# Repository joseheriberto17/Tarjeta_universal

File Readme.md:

# SSD1306 – UML del flujo actual (Mermaid)
**Autor:** jose heriberto  
**Fecha:** 2025-09-14  
**Propósito:** Documentar el flujo real del proyecto (init, armado de buffers, envío I²C, texto/figuras y scroll).  
**Ámbito:** App (main.c), Driver SSD1306 (cmd/ensamble), HAL/ASF (TWI0, PIO, PMC, SysTick).  
**Refs:** `SSD1306_cmd.c`, `SSD1306.h`, `main.c`

---

## 1) Vista de componentes (capas y dependencias)
```mermaid
flowchart TB
  subgraph App["App (main.c)"]
    Minit["sysclk_init/board_init\nconfigure_systick()\nconfigure_pins()"]
    Mdraw["Secuencia de dibujo:\nInicialize_SSD1306_default()\nNew_page()/frase_*/form_hearts()/vaciados()\nscroll() -> ssd1306_write()"]
    UART["UART_Handler (ISR)\n- lee RHR, limpia errores\n- eco debug"]
  end

  subgraph Driver["Driver SSD1306 (lógica de comandos)"]
    CMD["SSD1306_cmd.c\n(Set_*, Activate/Deactivate_Scroll,\nSet_Page_Start_..., etc.)"]
    BUF["Ensamble de buffer TWI\n(0x80 cmd-cont, 0x00 cmd-last,\n0xC0 data-cont, 0x40 data-last)"]
  end

  subgraph HAL["HAL / ASF (ATSAM3X8E)"]
    TWI["TWI0 (twi_master_init/twi_master_write)\nconfigure_pins_TWI_SSD1306()"]
    PIO["PIO (LEDs, mapeo pines)"]
    PMC["PMC clocks"]
    SysTick["SysTick (millis)"]
  end

  App --> Driver
  Driver --> HAL
  UART --> App
  Mdraw --> CMD
  CMD --> BUF
  Mdraw --> TWI
  BUF --> TWI
  Minit --> PMC
  Minit --> PIO
  Minit --> SysTick
```

---

## 2) Secuencia – Arranque e inicialización
```mermaid
sequenceDiagram
  autonumber
  participant Main as main.c
  participant HAL as HAL/ASF (PMC/PIO/SysTick)
  participant TWIc as configure_pins_TWI_SSD1306()
  participant CMD as Inicialize_SSD1306_default()
  participant BUF as Armado de buffer (0x80/0x00)
  participant I2C as ssd1306_write() / TWI0

  Main->>HAL: sysclk_init(), board_init()
  Main->>HAL: configure_systick()
  Main->>HAL: configure_pins() (LEDs)
  Main->>TWIc: configurar TWI0 (100 kHz) + pines PA17/PA18
  Main->>CMD: Inicialize_SSD1306_default(buffer_TWI, &len)
  activate CMD
  CMD->>BUF: Set_* cmds (AE, A8, D3, 40, A1, C8, DA, 81, A4/A5, A6/A7, D5, 8D, AF)
  BUF-->>CMD: buffer_TWI con parejas [0x80|0x00, cmd]
  deactivate CMD
  Main->>I2C: ssd1306_write(buffer_TWI, len*2)
  I2C-->>Main: status
```

---

## 3) Secuencia – Renderizado por páginas (texto/figuras/limpios y scroll)
```mermaid
sequenceDiagram
  autonumber
  participant Main as main.c
  participant CMD as New_page()/frase_A/B/C()/form_hearts()/vaciados()/scroll()
  participant BUF as Armado de buffer (0x80 cmd / 0xC0 data)
  participant I2C as ssd1306_write()/TWI0

  Main->>CMD: New_page(..., PAGE_0)
  CMD->>BUF: [0x80, B0|page] ... ultimo con 0x00
  BUF-->>Main: buffer_TWI, len
  Main->>I2C: ssd1306_write()
  end

  Main->>CMD: form_hearts()
  CMD->>BUF: datos con 0xC0 (cont.) y 0x40 (ultimo)
  BUF-->>Main: buffer_TWI (len=256)
  Main->>I2C: ssd1306_write(buffer_TWI, len)

  Note over Main: Vaciar paginas 1,2,6
  loop por cada pagina {1,2,6}
    Main->>CMD: New_page(PAGE_n)
    CMD->>BUF: comando B0|page (0x80...0x00)
    Main->>I2C: ssd1306_write(cmd)

    Main->>CMD: vaciados() (datos 0x00)
    CMD->>BUF: datos 0xC0...0x40
    Main->>I2C: ssd1306_write(data)
  end
  end

  Note over Main: Frases en paginas 3,4,5
  loop frase_A/B/C
    Main->>CMD: New_page(PAGE_k)
    CMD->>BUF: B0|page (0x80...0x00)
    Main->>I2C: ssd1306_write(cmd)

    Main->>CMD: frase_X() -> memcpy glyphs (128B)
    CMD->>BUF: datos 0xC0...0x40
    Main->>I2C: ssd1306_write(data)
  end
  end

  Note over Main: Scroll horizontal
  Main->>CMD
  CMD->>BUF: 0x26/0x27 + parametros; 0x2F (activate)
  end
  BUF-->>Main: buffer_TWI cmds (0x80...0x00)
  Main->>I2C: ssd1306_write(cmds scroll)
```

---

## 4) Máquina de estados – Driver/flujo SSD1306
```mermaid
stateDiagram-v2
  [*] --> Reset

  state Reset {
    note right: HW/SW reset
  }

  Reset --> InitSequence: Inicialize_SSD1306_default()
  InitSequence --> Ready: AF (Display ON) OK
  InitSequence --> Error: NAK / timeout

  Ready --> Updating: New_page()/frase_*/form_hearts()/vaciados()\n-> ssd1306_write(data)
  Updating --> Ready: última página/último byte (0x40) OK
  Updating --> Error: NAK / write fail

  Ready --> Scrolling: scroll() -> (0x26/0x27 ... 0x2F)
  Scrolling --> Ready: Deactivate_Scroll (0x2E) o redraw
  Scrolling --> Error: NAK

  Error --> Reset: política de reintento (max N)
```

---

## 5) Actividad – Ensamblado de buffer TWI (comandos y datos)
```mermaid
flowchart LR
  A[Iniciar buffer_TWI] --> B{¿Tipo?}
  B -- Comando --> C[Escribir 0x80 (continuación)\npara todos menos el último]
  C --> D[Escribir CMD]
  D --> E{¿Último comando del bloque?}
  E -- Sí --> F[Usar 0x00 en el último CMD]
  E -- No --> B

  B -- Datos --> G[Escribir 0xC0 (continuación)\npara todos menos el último]
  G --> H[Escribir DATA]
  H --> I{¿Último dato del bloque?}
  I -- Sí --> J[Usar 0x40 en el último DATA]
  I -- No --> B
```

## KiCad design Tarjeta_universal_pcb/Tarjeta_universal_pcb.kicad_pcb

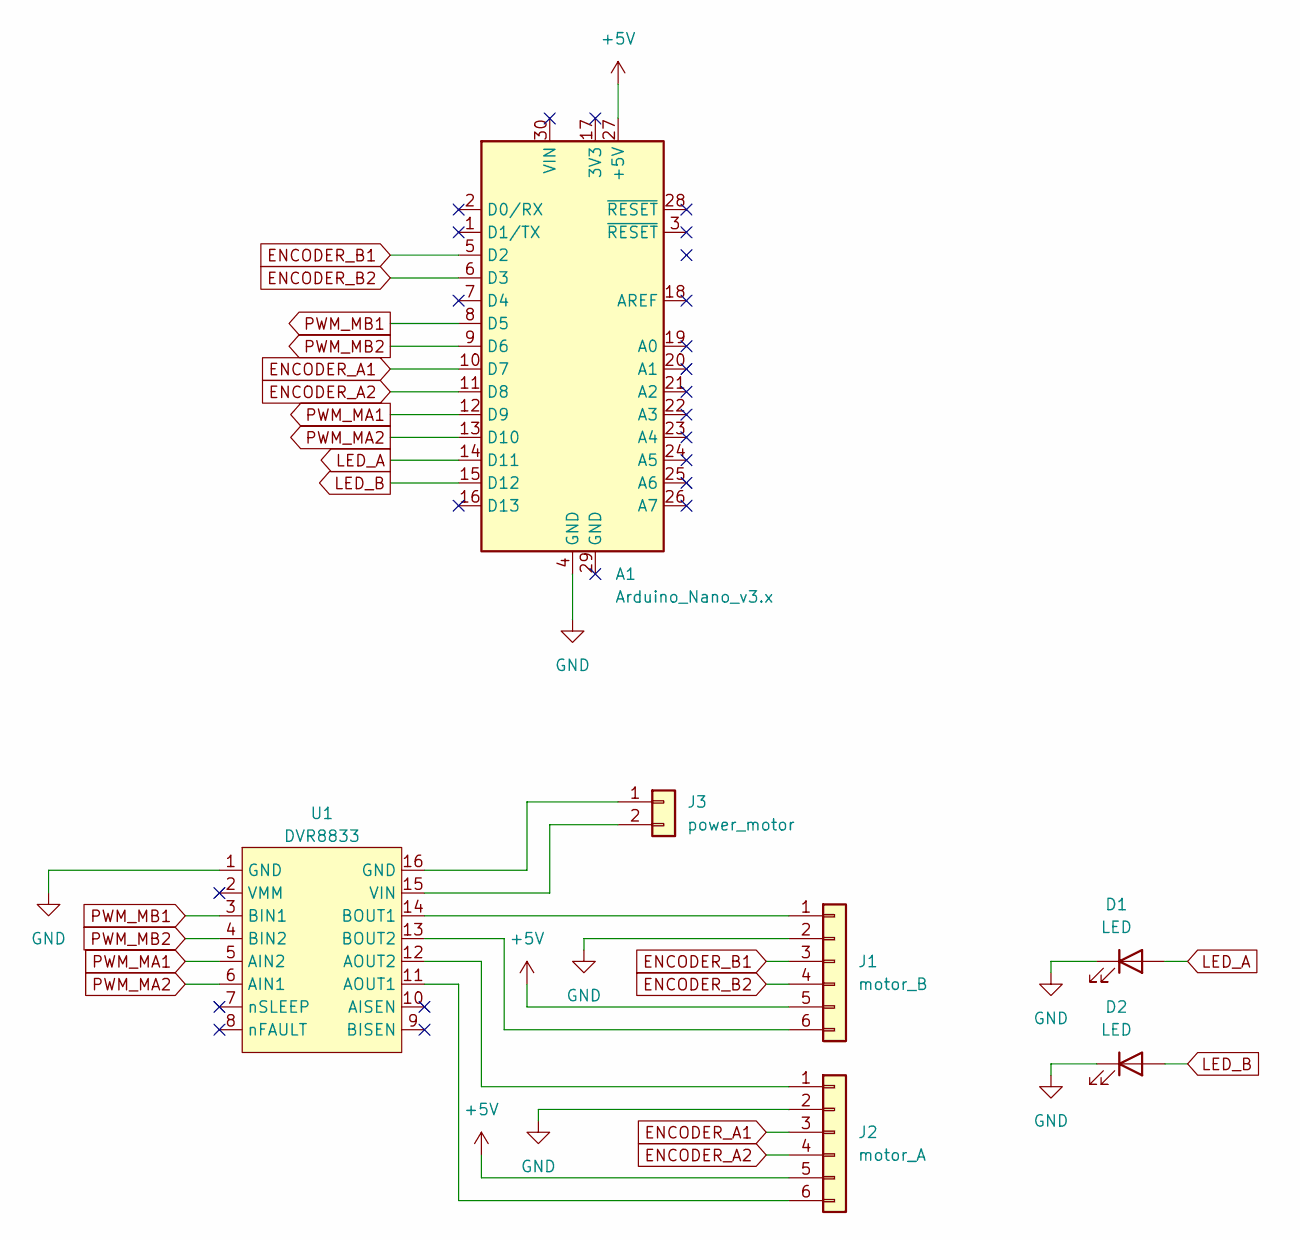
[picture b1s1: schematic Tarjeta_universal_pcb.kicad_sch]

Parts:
A1: Arduino_Nano_v3.x; Arduino_Nano
D1, D2: LED; LED_D3.0mm
J1: motor_B; PinHeader_1x06_P2.54mm_Vertical
J2: motor_A; PinHeader_1x06_P2.54mm_Vertical
J3: power_motor; PinHeader_1x02_P2.54mm_Vertical
U1: DVR8833; DIP-16_400_ELL

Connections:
+5V: A1.27 (+5V), J1.5, J2.5
ENCODER_A1: A1.10 (D7), J2.3
ENCODER_A2: A1.11 (D8), J2.4
ENCODER_B1: A1.5 (D2), J1.3
ENCODER_B2: A1.6 (D3), J1.4
GND: A1.4 (GND), D1.1 (K), D2.1 (K), J1.2, J2.2, U1.1 (GND)
LED_A: A1.14 (D11), D1.2 (A)
LED_B: A1.15 (D12), D2.2 (A)
unnamed: J1.1, U1.14 (BOUT1)
unnamed: J1.6, U1.13 (BOUT2)
unnamed: J2.1, U1.12 (AOUT2)
unnamed: J2.6, U1.11 (AOUT1)
unnamed: J3.1, U1.16 (GND)
unnamed: J3.2, U1.15 (VIN)
PWM_MA1: A1.12 (D9), U1.5 (AIN2)
PWM_MA2: A1.13 (D10), U1.6 (AIN1)
PWM_MB1: A1.8 (D5), U1.3 (BIN1)
PWM_MB2: A1.9 (D6), U1.4 (BIN2)

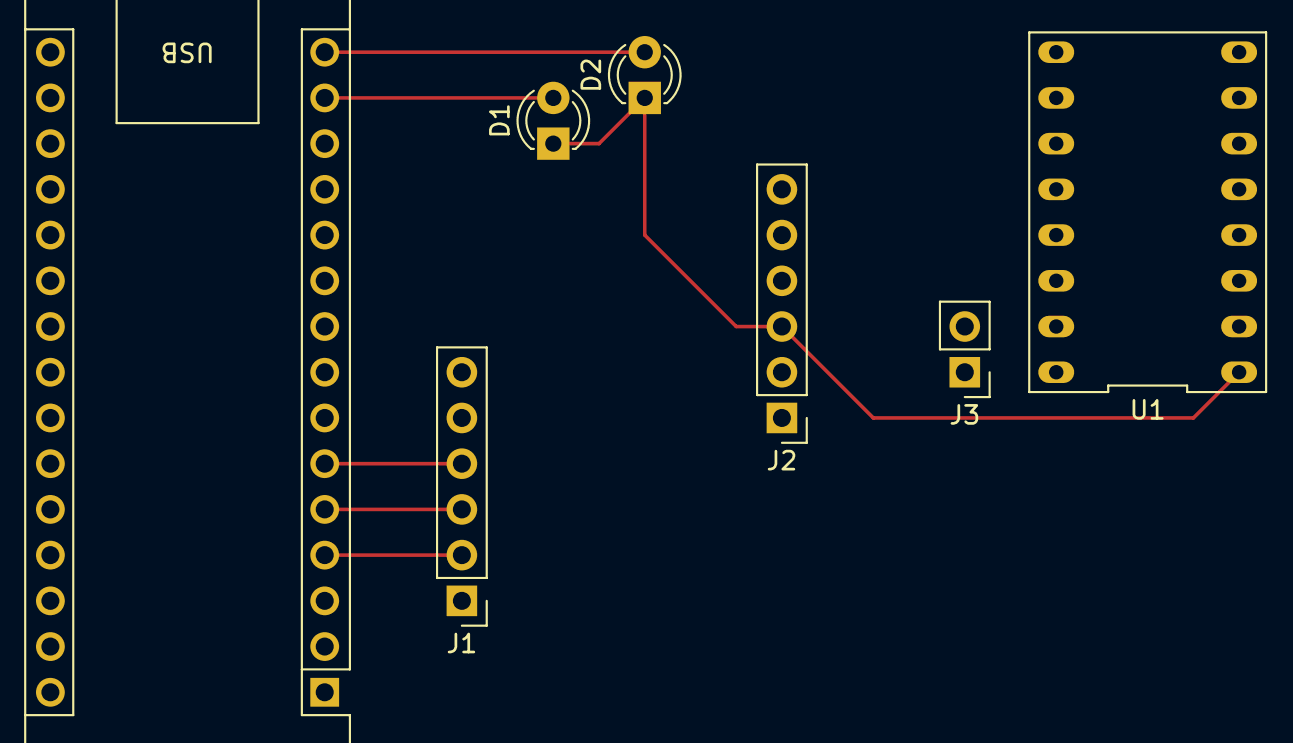
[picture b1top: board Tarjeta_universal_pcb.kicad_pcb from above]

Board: 2 copper layers, 7 parts (0 on the bottom side), 18 nets.

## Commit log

2025-06-25 inicio de repositorio
2025-07-20 Integracion de esquematico en el proyecto
    - se agrega gitignore el nuevo directorio de debug de proyecto de microchip studio
    - se agrega gitignore el contenido de directorio del esquemtatico no escencial
    - *-backups/
    - fp-info-cache/
    - *.kicad_prl
2025-07-20 subida del esquematico
2025-09-19 re estrucuracion de los directorios del proyecto
    Presente:
    - encoder, pwm pausado de da prieoria a la intefaz modulos de SS1306.
    - se modulaico parte de driver de la SSd1306 para falta organizalo.
    Futuro:
    - primero desaroolo de de ss1306-debug para una mejor comprension del driver.
    - continuacion de la modularidad del a intefaz de ssd1306.
